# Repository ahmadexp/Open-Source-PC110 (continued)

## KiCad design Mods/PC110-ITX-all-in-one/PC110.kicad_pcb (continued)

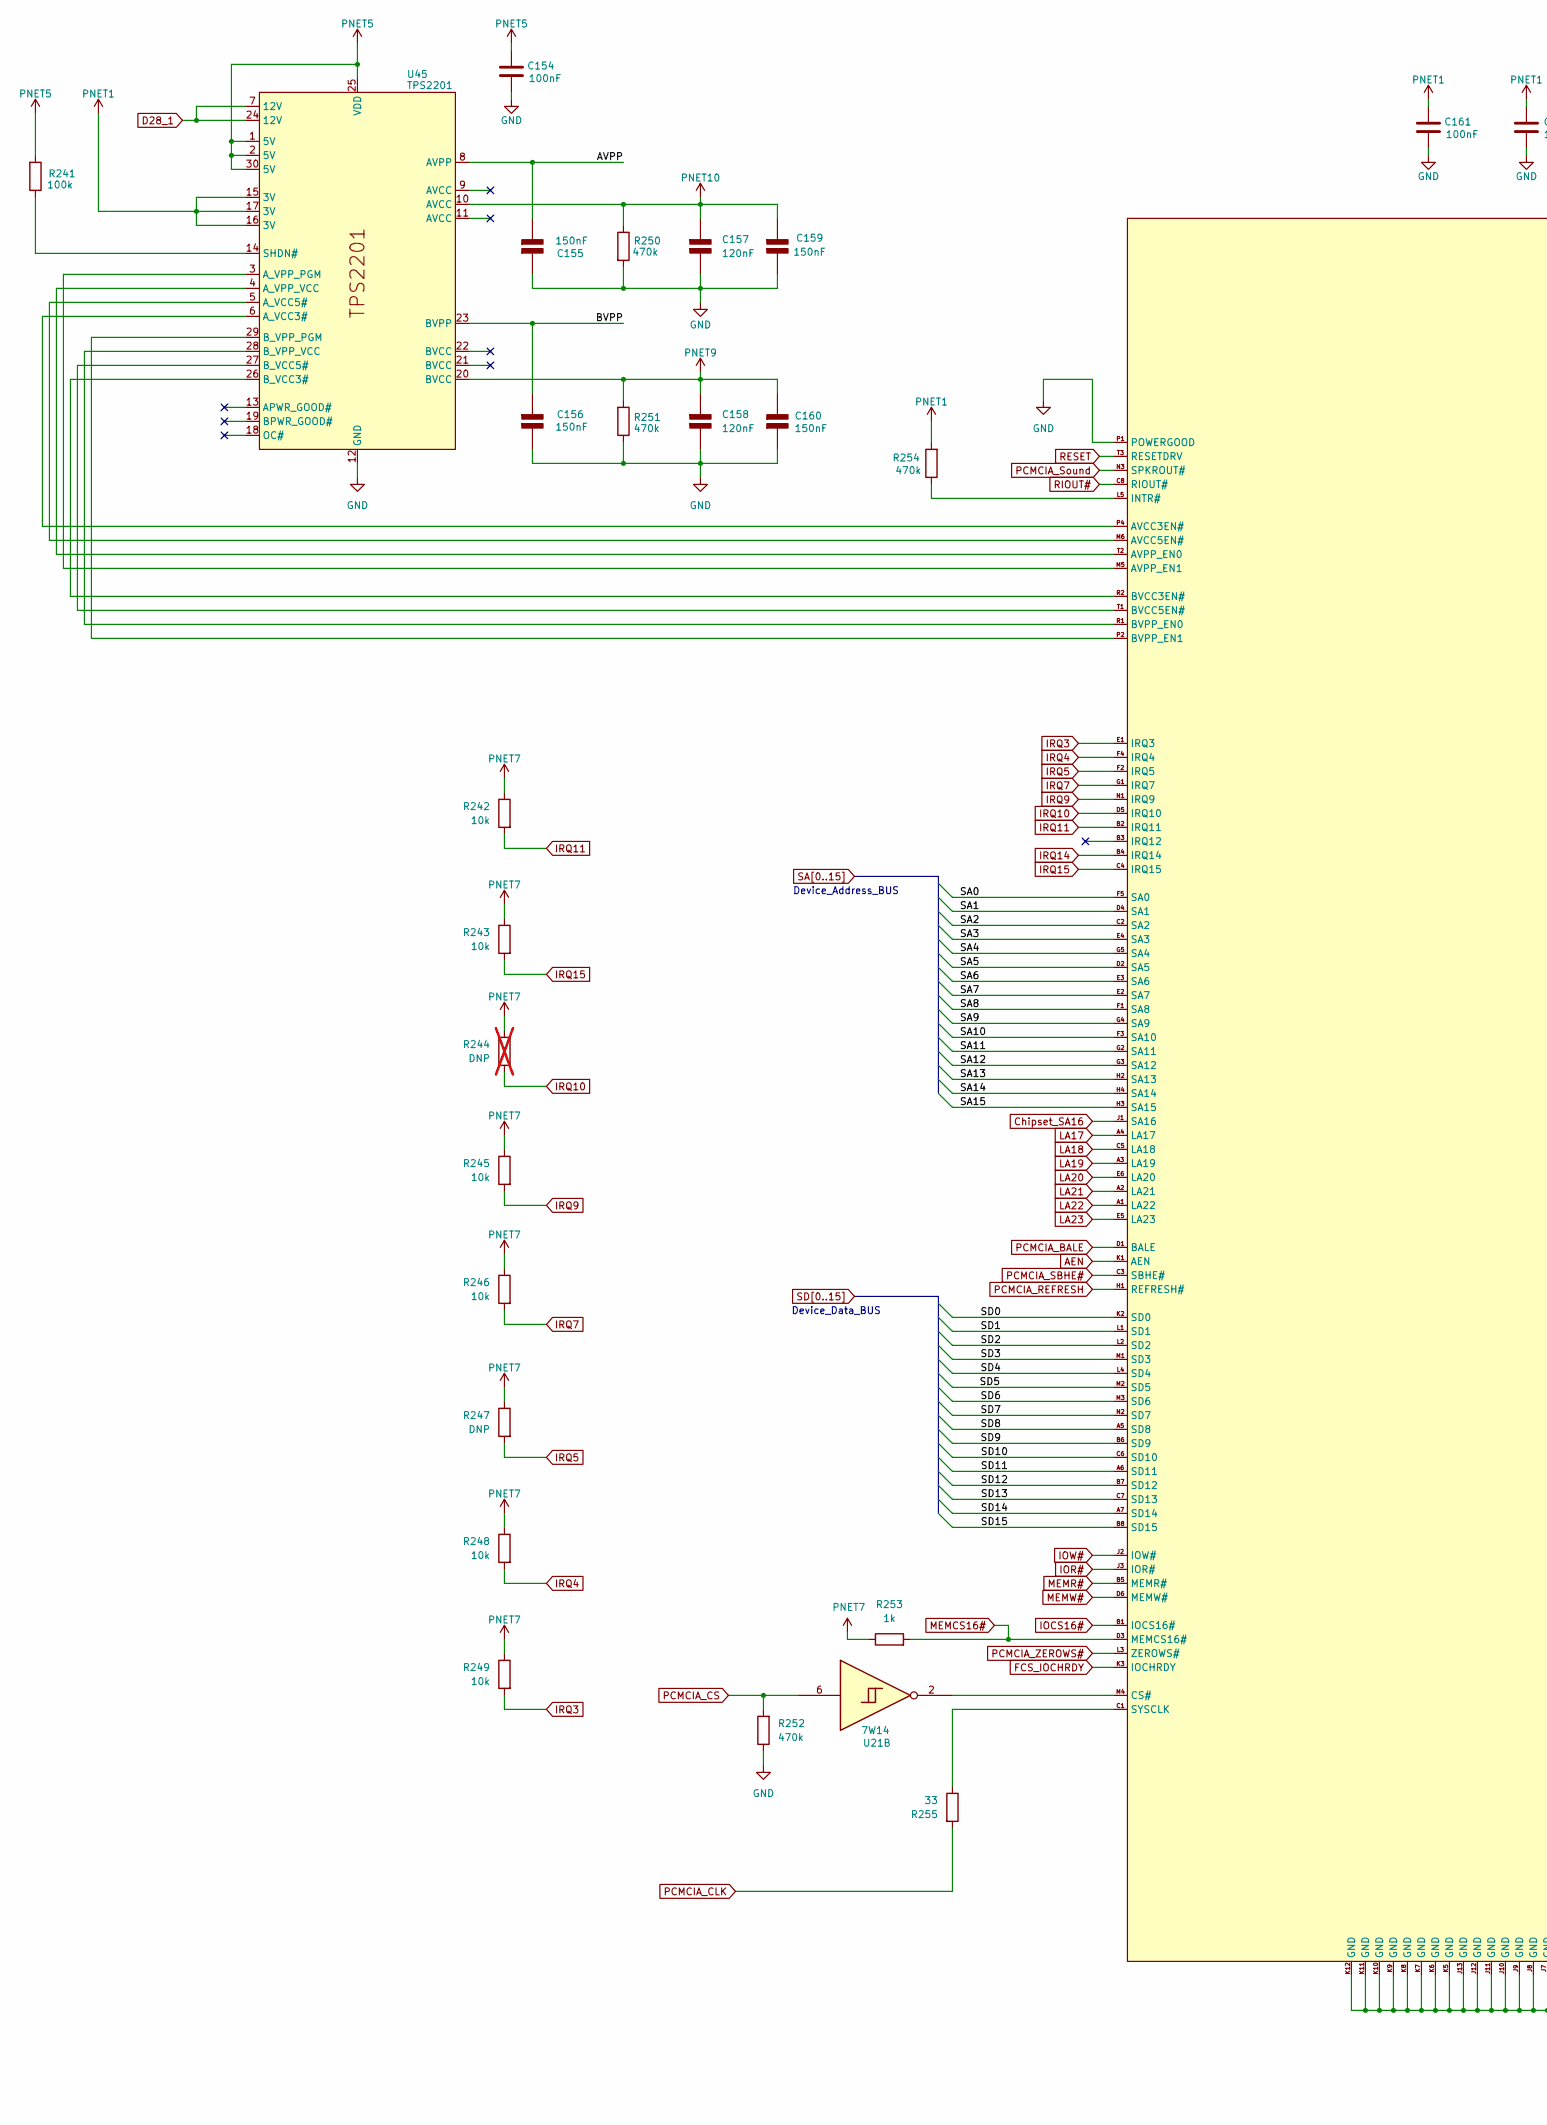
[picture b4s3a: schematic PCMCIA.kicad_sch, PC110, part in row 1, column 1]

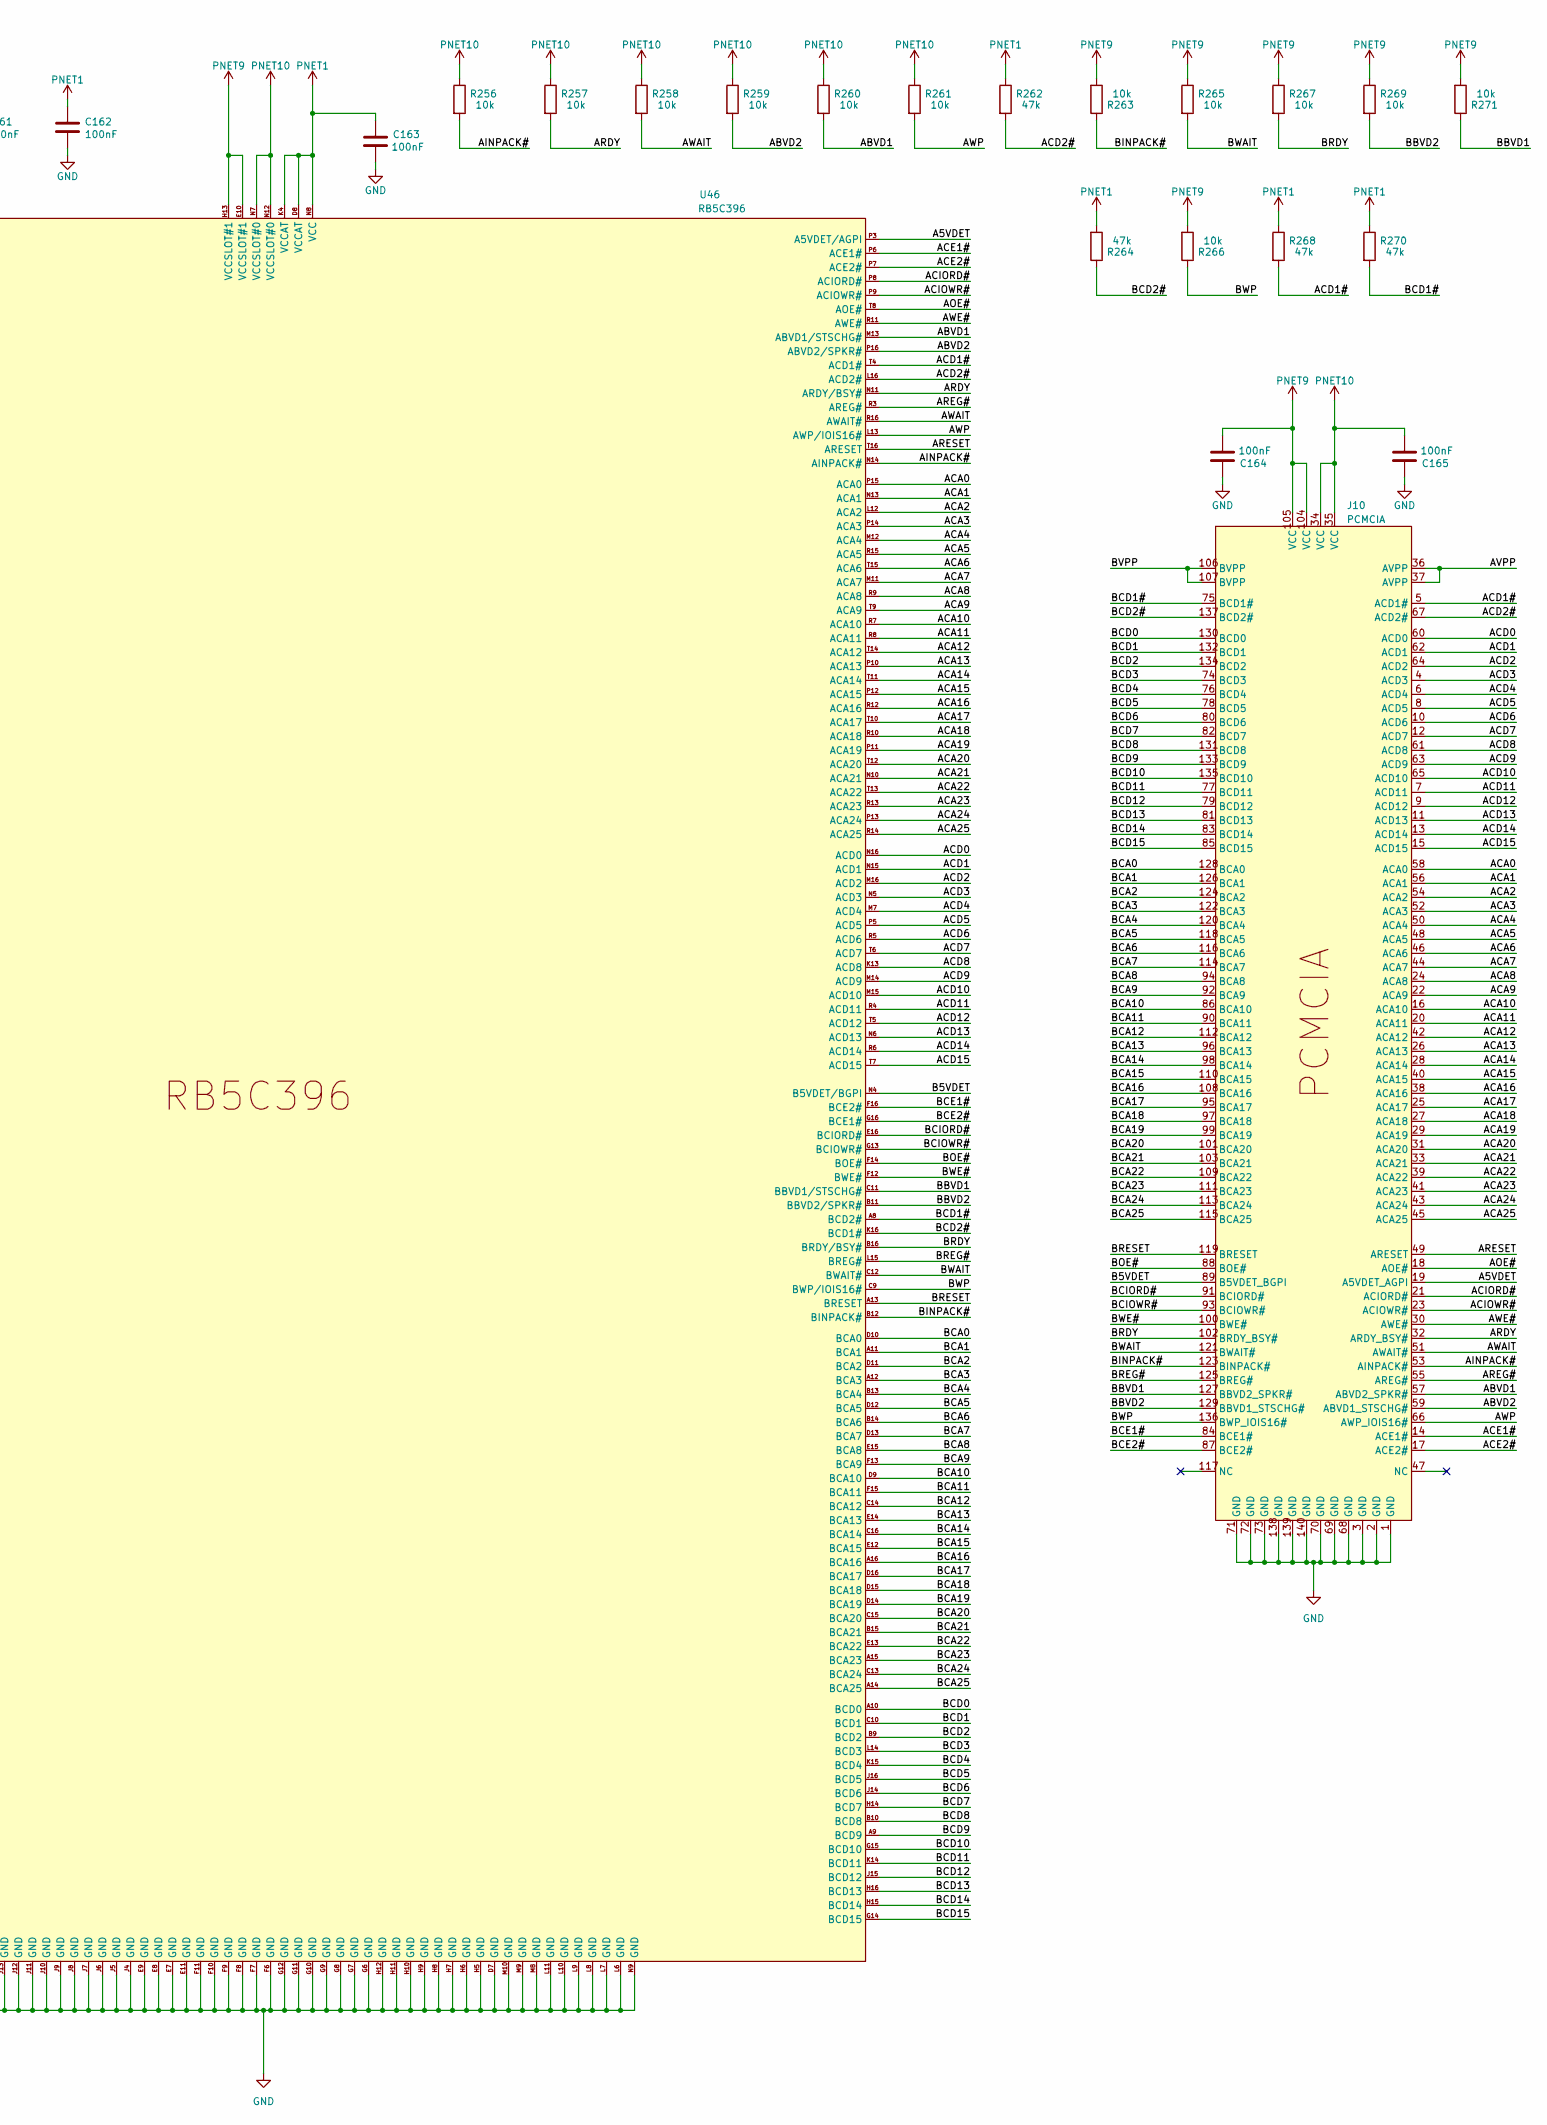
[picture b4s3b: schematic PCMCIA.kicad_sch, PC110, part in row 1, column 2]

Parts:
C154, C161, C162, C163, C164, C165: 100nF; C_0402_1005Metric
C155, C156: 150nF; C_0603_1608Metric
C157, C158: 120nF; C_0402_1005Metric
C159, C160: 150nF; C_0402_1005Metric
J10: PCMCIA
R241: 100k; R_0402_1005Metric
R242, R243, R245, R246, R248, R249, R256, R257, R258, R259, R260, R261, R263, R265, R266, R267, R269, R271: 10k; R_0402_1005Metric
R244: DNP; R_0402_1005Metric; not fitted
R247: DNP; R_0402_1005Metric
R250, R251, R252, R254: 470k; R_0402_1005Metric
R253: 1k; R_0402_1005Metric
R255: 33; R_0402_1005Metric
R262, R264, R268, R270: 47k; R_0402_1005Metric
U21: 7W14; sso-8
U45: TPS2201; TSSOP-30_6.1x9.7mm_P0.65mm
U46: RB5C396; BGA-256

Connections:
/PCMCIA/A5VDET: J10.19 (A5VDET_AGPI), U46.P3 (A5VDET/AGPI)
/PCMCIA/ABVD1: J10.57 (ABVD2_SPKR#), R260.2, U46.M13 (ABVD1/STSCHG#)
/PCMCIA/ABVD2: J10.59 (ABVD1_STSCHG#), R259.2, U46.P16 (ABVD2/SPKR#)
/PCMCIA/ACA0: J10.58 (ACA0), U46.P15 (ACA0)
/PCMCIA/ACA1: J10.56 (ACA1), U46.N13 (ACA1)
/PCMCIA/ACA2: J10.54 (ACA2), U46.L12 (ACA2)
/PCMCIA/ACA3: J10.52 (ACA3), U46.P14 (ACA3)
/PCMCIA/ACA4: J10.50 (ACA4), U46.M12 (ACA4)
/PCMCIA/ACA5: J10.48 (ACA5), U46.R15 (ACA5)
/PCMCIA/ACA6: J10.46 (ACA6), U46.T15 (ACA6)
/PCMCIA/ACA7: J10.44 (ACA7), U46.M11 (ACA7)
/PCMCIA/ACA8: J10.24 (ACA8), U46.R9 (ACA8)
/PCMCIA/ACA9: J10.22 (ACA9), U46.T9 (ACA9)
/PCMCIA/ACA10: J10.16 (ACA10), U46.R7 (ACA10)
/PCMCIA/ACA11: J10.20 (ACA11), U46.R8 (ACA11)
/PCMCIA/ACA12: J10.42 (ACA12), U46.T14 (ACA12)
/PCMCIA/ACA13: J10.26 (ACA13), U46.P10 (ACA13)
/PCMCIA/ACA14: J10.28 (ACA14), U46.T11 (ACA14)
/PCMCIA/ACA15: J10.40 (ACA15), U46.P12 (ACA15)
/PCMCIA/ACA16: J10.38 (ACA16), U46.R12 (ACA16)
/PCMCIA/ACA17: J10.25 (ACA17), U46.T10 (ACA17)
/PCMCIA/ACA18: J10.27 (ACA18), U46.R10 (ACA18)
/PCMCIA/ACA19: J10.29 (ACA19), U46.P11 (ACA19)
/PCMCIA/ACA20: J10.31 (ACA20), U46.T12 (ACA20)
/PCMCIA/ACA21: J10.33 (ACA21), U46.N10 (ACA21)
/PCMCIA/ACA22: J10.39 (ACA22), U46.T13 (ACA22)
/PCMCIA/ACA23: J10.41 (ACA23), U46.R13 (ACA23)
/PCMCIA/ACA24: J10.43 (ACA24), U46.P13 (ACA24)
/PCMCIA/ACA25: J10.45 (ACA25), U46.R14 (ACA25)
/PCMCIA/ACD0: J10.60 (ACD0), U46.N16 (ACD0)
/PCMCIA/ACD1: J10.62 (ACD1), U46.N15 (ACD1)
/PCMCIA/ACD1#: J10.5 (ACD1#), R268.2, U46.T4 (ACD1#)
/PCMCIA/ACD2: J10.64 (ACD2), U46.M16 (ACD2)
/PCMCIA/ACD2#: J10.67 (ACD2#), R262.2, U46.L16 (ACD2#)
/PCMCIA/ACD3: J10.4 (ACD3), U46.N5 (ACD3)
/PCMCIA/ACD4: J10.6 (ACD4), U46.M7 (ACD4)
/PCMCIA/ACD5: J10.8 (ACD5), U46.P5 (ACD5)
/PCMCIA/ACD6: J10.10 (ACD6), U46.R5 (ACD6)
/PCMCIA/ACD7: J10.12 (ACD7), U46.T6 (ACD7)
/PCMCIA/ACD8: J10.61 (ACD8), U46.K13 (ACD8)
/PCMCIA/ACD9: J10.63 (ACD9), U46.M14 (ACD9)
/PCMCIA/ACD10: J10.65 (ACD10), U46.M15 (ACD10)
/PCMCIA/ACD11: J10.7 (ACD11), U46.R4 (ACD11)
/PCMCIA/ACD12: J10.9 (ACD12), U46.T5 (ACD12)
/PCMCIA/ACD13: J10.11 (ACD13), U46.N6 (ACD13)
/PCMCIA/ACD14: J10.13 (ACD14), U46.R6 (ACD14)
/PCMCIA/ACD15: J10.15 (ACD15), U46.T7 (ACD15)
/PCMCIA/ACE1#: J10.14 (ACE1#), U46.P6 (ACE1#)
/PCMCIA/ACE2#: J10.17 (ACE2#), U46.P7 (ACE2#)
/PCMCIA/ACIORD#: J10.21 (ACIORD#), U46.P8 (ACIORD#)
/PCMCIA/ACIOWR#: J10.23 (ACIOWR#), U46.P9 (ACIOWR#)
/PCMCIA/AINPACK#: J10.53 (AINPACK#), R256.2, U46.N14 (AINPACK#)
/PCMCIA/AOE#: J10.18 (AOE#), U46.T8 (AOE#)
/PCMCIA/ARDY: J10.32 (ARDY_BSY#), R257.2, U46.N11 (ARDY/BSY#)
/PCMCIA/AREG#: J10.55 (AREG#), U46.R3 (AREG#)
/PCMCIA/ARESET: J10.49 (ARESET), U46.T16 (ARESET)
/PCMCIA/AVPP: C155.2 (-), J10.36 (AVPP), J10.37 (AVPP), U45.8 (AVPP)
/PCMCIA/AWAIT: J10.51 (AWAIT#), R258.2, U46.R16 (AWAIT#)
/PCMCIA/AWE#: J10.30 (AWE#), U46.R11 (AWE#)
/PCMCIA/AWP: J10.66 (AWP_IOIS16#), R261.2, U46.L13 (AWP/IOIS16#)
/PCMCIA/B5VDET: J10.89 (B5VDET_BGPI), U46.N4 (B5VDET/BGPI)
/PCMCIA/BBVD1: J10.127 (BBVD2_SPKR#), R271.1, U46.C11 (BBVD1/STSCHG#)
/PCMCIA/BBVD2: J10.129 (BBVD1_STSCHG#), R269.2, U46.B11 (BBVD2/SPKR#)
/PCMCIA/BCA0: J10.128 (BCA0), U46.D10 (BCA0)
/PCMCIA/BCA1: J10.126 (BCA1), U46.A11 (BCA1)
/PCMCIA/BCA2: J10.124 (BCA2), U46.D11 (BCA2)
/PCMCIA/BCA3: J10.122 (BCA3), U46.A12 (BCA3)
/PCMCIA/BCA4: J10.120 (BCA4), U46.B13 (BCA4)
/PCMCIA/BCA5: J10.118 (BCA5), U46.D12 (BCA5)
/PCMCIA/BCA6: J10.116 (BCA6), U46.B14 (BCA6)
/PCMCIA/BCA7: J10.114 (BCA7), U46.D13 (BCA7)
/PCMCIA/BCA8: J10.94 (BCA8), U46.E15 (BCA8)
/PCMCIA/BCA9: J10.92 (BCA9), U46.F13 (BCA9)
/PCMCIA/BCA10: J10.86 (BCA10), U46.D9 (BCA10)
/PCMCIA/BCA11: J10.90 (BCA11), U46.F15 (BCA11)
/PCMCIA/BCA12: J10.112 (BCA12), U46.C14 (BCA12)
/PCMCIA/BCA13: J10.96 (BCA13), U46.E14 (BCA13)
/PCMCIA/BCA14: J10.98 (BCA14), U46.C16 (BCA14)
/PCMCIA/BCA15: J10.110 (BCA15), U46.E12 (BCA15)
/PCMCIA/BCA16: J10.108 (BCA16), U46.A16 (BCA16)
/PCMCIA/BCA17: J10.95 (BCA17), U46.D16 (BCA17)
/PCMCIA/BCA18: J10.97 (BCA18), U46.D15 (BCA18)
/PCMCIA/BCA19: J10.99 (BCA19), U46.D14 (BCA19)
/PCMCIA/BCA20: J10.101 (BCA20), U46.C15 (BCA20)
/PCMCIA/BCA21: J10.103 (BCA21), U46.B15 (BCA21)
/PCMCIA/BCA22: J10.109 (BCA22), U46.E13 (BCA22)
/PCMCIA/BCA23: J10.111 (BCA23), U46.A15 (BCA23)
/PCMCIA/BCA24: J10.113 (BCA24), U46.C13 (BCA24)
/PCMCIA/BCA25: J10.115 (BCA25), U46.A14 (BCA25)
/PCMCIA/BCD0: J10.130 (BCD0), U46.A10 (BCD0)
/PCMCIA/BCD1: J10.132 (BCD1), U46.C10 (BCD1)
/PCMCIA/BCD1#: J10.75 (BCD1#), R270.2, U46.A8 (BCD2#)
/PCMCIA/BCD2: J10.134 (BCD2), U46.B9 (BCD2)
/PCMCIA/BCD2#: J10.137 (BCD2#), R264.1, U46.K16 (BCD1#)
/PCMCIA/BCD3: J10.74 (BCD3), U46.L14 (BCD3)
/PCMCIA/BCD4: J10.76 (BCD4), U46.K15 (BCD4)
/PCMCIA/BCD5: J10.78 (BCD5), U46.J16 (BCD5)
/PCMCIA/BCD6: J10.80 (BCD6), U46.J14 (BCD6)
/PCMCIA/BCD7: J10.82 (BCD7), U46.H14 (BCD7)
/PCMCIA/BCD8: J10.131 (BCD8), U46.B10 (BCD8)
/PCMCIA/BCD9: J10.133 (BCD9), U46.A9 (BCD9)
/PCMCIA/BCD10: J10.135 (BCD10), U46.G15 (BCD10)
/PCMCIA/BCD11: J10.77 (BCD11), U46.K14 (BCD11)
/PCMCIA/BCD12: J10.79 (BCD12), U46.J15 (BCD12)
/PCMCIA/BCD13: J10.81 (BCD13), U46.H16 (BCD13)
/PCMCIA/BCD14: J10.83 (BCD14), U46.H15 (BCD14)
/PCMCIA/BCD15: J10.85 (BCD15), U46.G14 (BCD15)
/PCMCIA/BCE1#: J10.84 (BCE1#), U46.F16 (BCE2#)
/PCMCIA/BCE2#: J10.87 (BCE2#), U46.G16 (BCE1#)
/PCMCIA/BCIORD#: J10.91 (BCIORD#), U46.E16 (BCIORD#)
/PCMCIA/BCIOWR#: J10.93 (BCIOWR#), U46.G13 (BCIOWR#)
/PCMCIA/BINPACK#: J10.123 (BINPACK#), R263.1, U46.B12 (BINPACK#)
/PCMCIA/BOE#: J10.88 (BOE#), U46.F14 (BOE#)
/PCMCIA/BRDY: J10.102 (BRDY_BSY#), R267.2, U46.B16 (BRDY/BSY#)
/PCMCIA/BREG#: J10.125 (BREG#), U46.L15 (BREG#)
/PCMCIA/BRESET: J10.119 (BRESET), U46.A13 (BRESET)
/PCMCIA/BVPP: C156.1 (+), J10.106 (BVPP), J10.107 (BVPP), U45.23 (BVPP)
/PCMCIA/BWAIT: J10.121 (BWAIT#), R265.2, U46.C12 (BWAIT#)
/PCMCIA/BWE#: J10.100 (BWE#), U46.F12 (BWE#)
/PCMCIA/BWP: J10.136 (BWP_IOIS16#), R266.1, U46.C9 (BWP/IOIS16#)
AEN: U46.K1 (AEN); also elsewhere on the board
Chipset_SA16: U46.J1 (SA16); also elsewhere on the board
D28_1: U45.7 (12V), U45.24 (12V); also elsewhere on the board
FCS_IOCHRDY: U46.K3 (IOCHRDY); also elsewhere on the board
GND: C154.2, C155.1 (+), C156.2 (-), C157.2 (-), C158.2 (-), C159.2 (-), C160.1 (+), C161.2, C162.2, C163.1, C164.2, C165.2, J10.1 (GND), J10.2 (GND), J10.3 (GND), J10.68 (GND), J10.69 (GND), J10.70 (GND), J10.71 (GND), J10.72 (GND), J10.73 (GND), J10.138 (GND), J10.139 (GND), J10.140 (GND), R250.2, R251.1, R252.1, U45.12 (GND), U46.D7 (GND), U46.E7 (GND), U46.E8 (GND), U46.E9 (GND), U46.E11 (GND), U46.F6 (GND), U46.F7 (GND), U46.F8 (GND), U46.F9 (GND), U46.F10 (GND), U46.F11 (GND), U46.G6 (GND), U46.G7 (GND), U46.G8 (GND), U46.G9 (GND), U46.G10 (GND), U46.G11 (GND), U46.G12 (GND), U46.H5 (GND), U46.H6 (GND), U46.H7 (GND), U46.H8 (GND), U46.H9 (GND), U46.H10 (GND), U46.H11 (GND), U46.H12 (GND), U46.J4 (GND), U46.J5 (GND), U46.J6 (GND), U46.J7 (GND), U46.J8 (GND), U46.J9 (GND), U46.J10 (GND), U46.J11 (GND), U46.J12 (GND), U46.J13 (GND), U46.K5 (GND), U46.K6 (GND), U46.K7 (GND), U46.K8 (GND), U46.K9 (GND), U46.K10 (GND), U46.K11 (GND), U46.K12 (GND), U46.L6 (GND), U46.L7 (GND), U46.L8 (GND), U46.L9 (GND), U46.L10 (GND), U46.L11 (GND), U46.M8 (GND), U46.M9 (GND), U46.M10 (GND), U46.N9 (GND), U46.P1 (POWERGOOD); also elsewhere on the board
IOCS16#: U46.B1 (IOCS16#); also elsewhere on the board
IOR#: U46.J3 (IOR#); also elsewhere on the board
IOW#: U46.J2 (IOW#); also elsewhere on the board
IRQ3: R249.2, U46.E1 (IRQ3); also elsewhere on the board
IRQ4: R248.2, U46.F4 (IRQ4); also elsewhere on the board
IRQ5: R247.2, U46.F2 (IRQ5); also elsewhere on the board
IRQ7: R246.2, U46.G1 (IRQ7); also elsewhere on the board
IRQ9: R245.2, U46.N1 (IRQ9); also elsewhere on the board
IRQ10: R244.2, U46.D5 (IRQ10); also elsewhere on the board
IRQ11: R242.2, U46.B2 (IRQ11); also elsewhere on the board
IRQ14: U46.B4 (IRQ14); also elsewhere on the board
IRQ15: R243.2, U46.C4 (IRQ15); also elsewhere on the board
LA17: U46.A4 (LA17); also elsewhere on the board
LA18: U46.C5 (LA18); also elsewhere on the board
LA19: U46.A3 (LA19); also elsewhere on the board
LA20: U46.E6 (LA20); also elsewhere on the board
LA21: U46.A2 (LA21); also elsewhere on the board
LA22: U46.A1 (LA22); also elsewhere on the board
LA23: U46.E5 (LA23); also elsewhere on the board
MEMCS16#: R253.2, U46.D3 (MEMCS16#); also elsewhere on the board
MEMR#: U46.B5 (MEMR#); also elsewhere on the board
MEMW#: U46.D6 (MEMW#); also elsewhere on the board
unnamed: U45.6 (A_VCC3#), U46.P4 (AVCC3EN#)
unnamed: U45.5 (A_VCC5#), U46.M6 (AVCC5EN#)
unnamed: U45.3 (A_VPP_PGM), U46.M5 (AVPP_EN1)
unnamed: U45.4 (A_VPP_VCC), U46.T2 (AVPP_EN0)
unnamed: U45.26 (B_VCC3#), U46.R2 (BVCC3EN#)
unnamed: U45.27 (B_VCC5#), U46.T1 (BVCC5EN#)
unnamed: U45.29 (B_VPP_PGM), U46.P2 (BVPP_EN1)
unnamed: U45.28 (B_VPP_VCC), U46.R1 (BVPP_EN0)
unnamed: R241.1, U45.14 (SHDN#)
unnamed: U21.2, U46.M4 (CS#)
unnamed: R254.1, U46.L5 (INTR#)
unnamed: R255.1, U46.C1 (SYSCLK)
PCMCIA_BALE: U46.D1 (BALE); also elsewhere on the board
PCMCIA_CLK: R255.2; also elsewhere on the board
PCMCIA_CS: R252.2, U21.6; also elsewhere on the board
PCMCIA_REFRESH: U46.H1 (REFRESH#); also elsewhere on the board
PCMCIA_SBHE#: U46.C3 (SBHE#); also elsewhere on the board
PCMCIA_Sound: U46.N3 (SPKROUT#); also elsewhere on the board
PCMCIA_ZEROWS#: U46.L3 (ZEROWS#); also elsewhere on the board
PNET1: C161.1, C162.1, C163.2, R254.2, R262.1, R264.2, R268.1, R270.1, U45.15 (3V), U45.16 (3V), U45.17 (3V), U46.D8 (VCCAT), U46.K4 (VCCAT), U46.N8 (VCC); also elsewhere on the board
PNET5: C154.1, R241.2, U45.1 (5V), U45.2 (5V), U45.25 (VDD), U45.30 (5V); also elsewhere on the board
PNET7: R242.1, R243.1, R244.1, R245.1, R246.1, R247.1, R248.1, R249.1, R253.1; also elsewhere on the board
PNET9: C158.1 (+), C160.2 (-), C164.1, J10.104 (VCC), J10.105 (VCC), R251.2, R263.2, R265.1, R266.2, R267.1, R269.1, R271.2, U45.20 (BVCC), U46.E10 (VCCSLOT#1), U46.H13 (VCCSLOT#1)
PNET10: C157.1 (+), C159.1 (+), C165.1, J10.34 (VCC), J10.35 (VCC), R250.1, R256.1, R257.1, R258.1, R259.1, R260.1, R261.1, U45.10 (AVCC), U46.N7 (VCCSLOT#0), U46.N12 (VCCSLOT#0)
RESET: U46.T3 (RESETDRV); also elsewhere on the board
RIOUT#: U46.C8 (RIOUT#); also elsewhere on the board
SA0: U46.F5 (SA0); also elsewhere on the board
SA1: U46.D4 (SA1); also elsewhere on the board
SA2: U46.C2 (SA2); also elsewhere on the board
SA3: U46.E4 (SA3); also elsewhere on the board
SA4: U46.G5 (SA4); also elsewhere on the board
SA5: U46.D2 (SA5); also elsewhere on the board
SA6: U46.E3 (SA6); also elsewhere on the board
SA7: U46.E2 (SA7); also elsewhere on the board
SA8: U46.F1 (SA8); also elsewhere on the board
SA9: U46.G4 (SA9); also elsewhere on the board
SA10: U46.F3 (SA10); also elsewhere on the board
SA11: U46.G2 (SA11); also elsewhere on the board
SA12: U46.G3 (SA12); also elsewhere on the board
SA13: U46.H2 (SA13); also elsewhere on the board
SA14: U46.H4 (SA14); also elsewhere on the board
SA15: U46.H3 (SA15); also elsewhere on the board
SD0: U46.K2 (SD0); also elsewhere on the board
SD1: U46.L1 (SD1); also elsewhere on the board
SD2: U46.L2 (SD2); also elsewhere on the board
SD3: U46.M1 (SD3); also elsewhere on the board
SD4: U46.L4 (SD4); also elsewhere on the board
SD5: U46.M2 (SD5); also elsewhere on the board
SD6: U46.M3 (SD6); also elsewhere on the board
SD7: U46.N2 (SD7); also elsewhere on the board
SD8: U46.A5 (SD8); also elsewhere on the board
SD9: U46.B6 (SD9); also elsewhere on the board
SD10: U46.C6 (SD10); also elsewhere on the board
SD11: U46.A6 (SD11); also elsewhere on the board
SD12: U46.B7 (SD12); also elsewhere on the board
SD13: U46.C7 (SD13); also elsewhere on the board
SD14: U46.A7 (SD14); also elsewhere on the board
SD15: U46.B8 (SD15); also elsewhere on the board

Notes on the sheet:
Device_Data_BUS
Device_Address_BUS

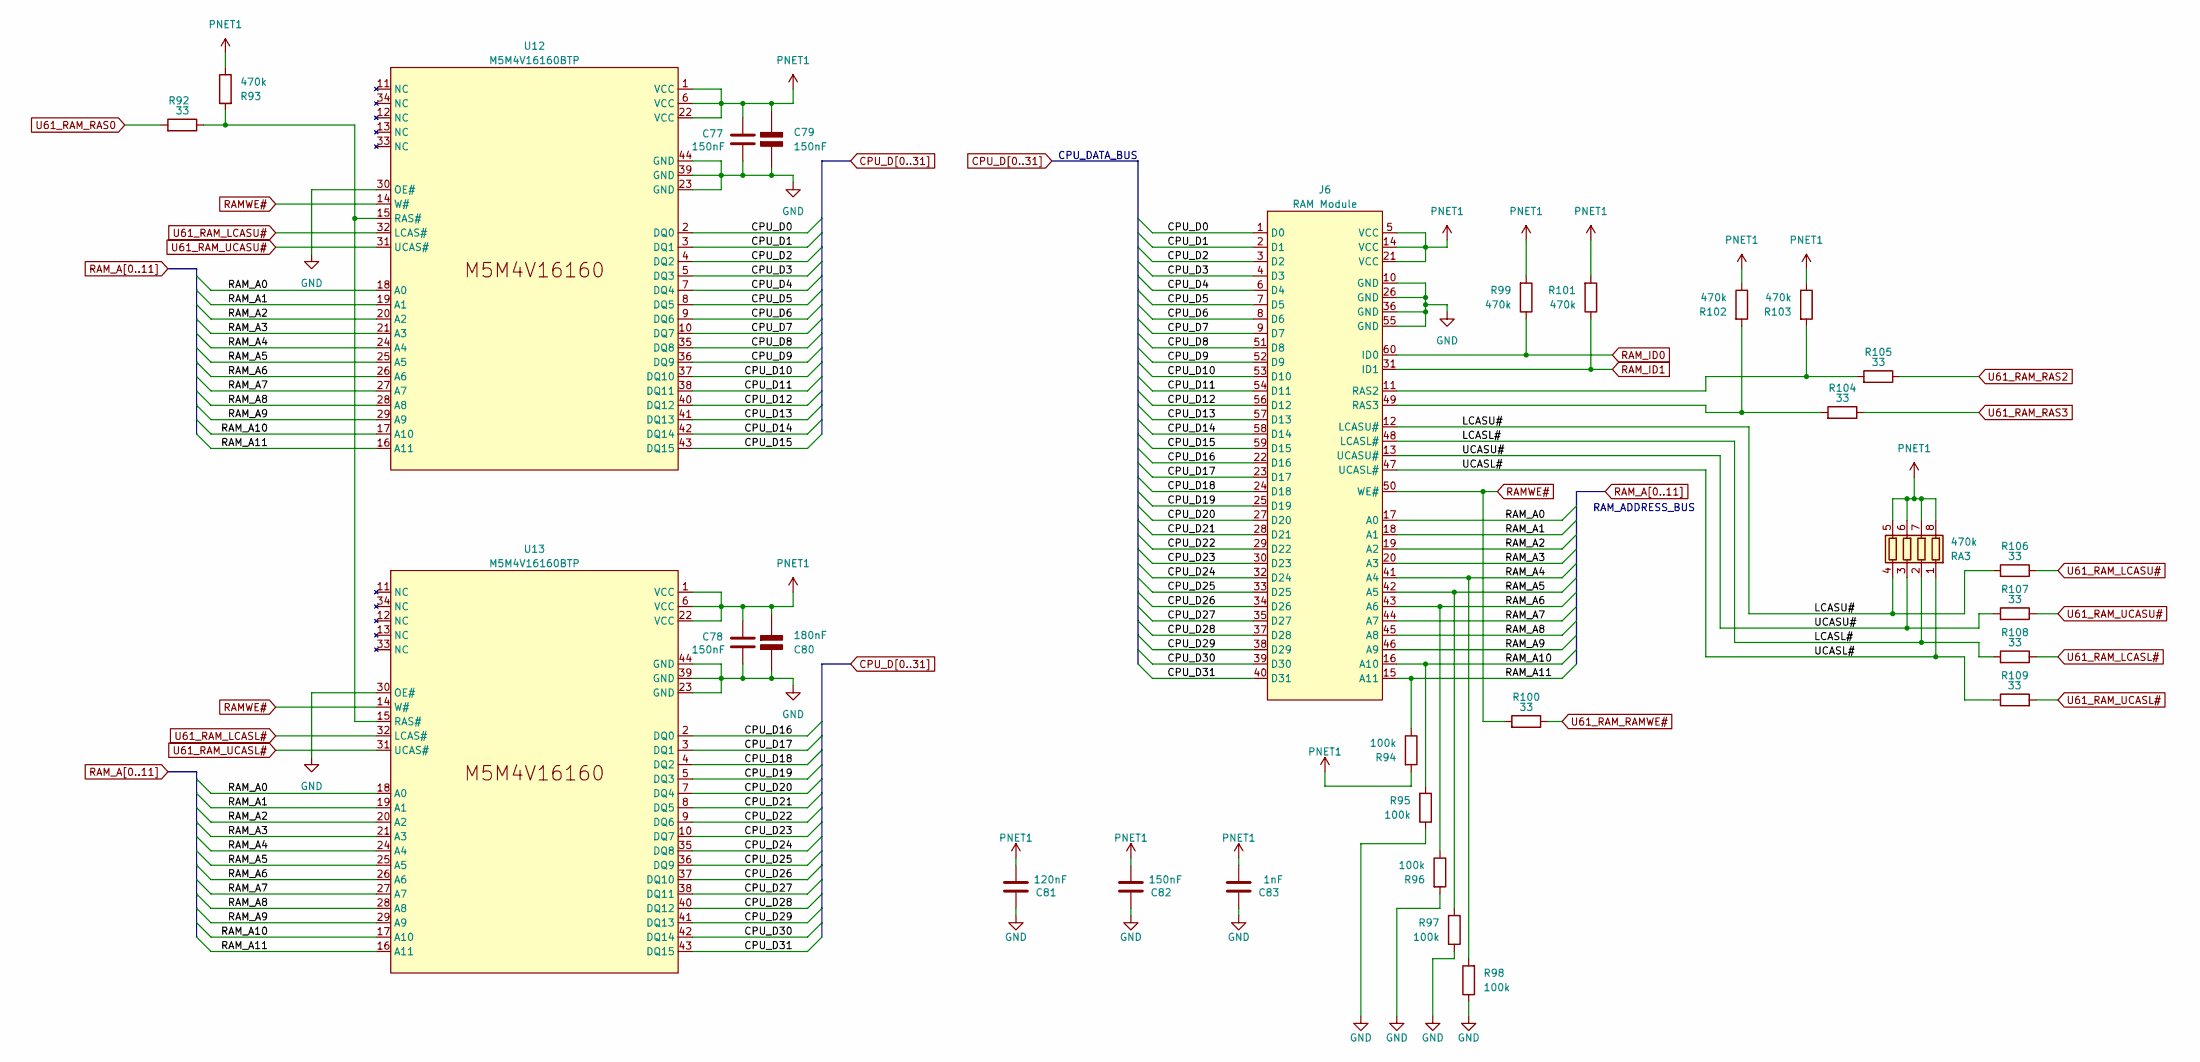
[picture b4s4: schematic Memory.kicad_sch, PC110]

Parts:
C77, C78, C79, C82: 150nF; C_0402_1005Metric
C80: 180nF; C_0402_1005Metric
C81: 120nF; C_0402_1005Metric
C83: 1nF; C_0402_1005Metric
J6: RAM Module
R92, R100, R104, R105, R106, R107, R108, R109: 33; R_0402_1005Metric
R93, R99, R101, R102, R103: 470k; R_0402_1005Metric
R94, R95, R96, R97, R98: 100k; R_0402_1005Metric
RA3: 470k; R-array
U12, U13: M5M4V16160BTP; RAMchip

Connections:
/Memory/LCASL#: J6.48 (LCASL#), R108.2, RA3.2 (R2.1)
/Memory/LCASU#: J6.12 (LCASU#), R106.2, RA3.4 (R4.1)
/Memory/UCASL#: J6.47 (UCASL#), R109.1, RA3.1 (R1.1)
/Memory/UCASU#: J6.13 (UCASU#), R107.2, RA3.3 (R3.1)
CPU_D0: J6.1 (D0), U12.2 (DQ0); also elsewhere on the board
CPU_D1: J6.2 (D1), U12.3 (DQ1); also elsewhere on the board
CPU_D2: J6.3 (D2), U12.4 (DQ2); also elsewhere on the board
CPU_D3: J6.4 (D3), U12.5 (DQ3); also elsewhere on the board
CPU_D4: J6.6 (D4), U12.7 (DQ4); also elsewhere on the board
CPU_D5: J6.7 (D5), U12.8 (DQ5); also elsewhere on the board
CPU_D6: J6.8 (D6), U12.9 (DQ6); also elsewhere on the board
CPU_D7: J6.9 (D7), U12.10 (DQ7); also elsewhere on the board
CPU_D8: J6.51 (D8), U12.35 (DQ8); also elsewhere on the board
CPU_D9: J6.52 (D9), U12.36 (DQ9); also elsewhere on the board
CPU_D10: J6.53 (D10), U12.37 (DQ10); also elsewhere on the board
CPU_D11: J6.54 (D11), U12.38 (DQ11); also elsewhere on the board
CPU_D12: J6.56 (D12), U12.40 (DQ12); also elsewhere on the board
CPU_D13: J6.57 (D13), U12.41 (DQ13); also elsewhere on the board
CPU_D14: J6.58 (D14), U12.42 (DQ14); also elsewhere on the board
CPU_D15: J6.59 (D15), U12.43 (DQ15); also elsewhere on the board
CPU_D16: J6.22 (D16), U13.2 (DQ0); also elsewhere on the board
CPU_D17: J6.23 (D17), U13.3 (DQ1); also elsewhere on the board
CPU_D18: J6.24 (D18), U13.4 (DQ2); also elsewhere on the board
CPU_D19: J6.25 (D19), U13.5 (DQ3); also elsewhere on the board
CPU_D20: J6.27 (D20), U13.7 (DQ4); also elsewhere on the board
CPU_D21: J6.28 (D21), U13.8 (DQ5); also elsewhere on the board
CPU_D22: J6.29 (D22), U13.9 (DQ6); also elsewhere on the board
CPU_D23: J6.30 (D23), U13.10 (DQ7); also elsewhere on the board
CPU_D24: J6.32 (D24), U13.35 (DQ8); also elsewhere on the board
CPU_D25: J6.33 (D25), U13.36 (DQ9); also elsewhere on the board
CPU_D26: J6.34 (D26), U13.37 (DQ10); also elsewhere on the board
CPU_D27: J6.35 (D27), U13.38 (DQ11); also elsewhere on the board
CPU_D28: J6.37 (D28), U13.40 (DQ12); also elsewhere on the board
CPU_D29: J6.38 (D29), U13.41 (DQ13); also elsewhere on the board
CPU_D30: J6.39 (D30), U13.42 (DQ14); also elsewhere on the board
CPU_D31: J6.40 (D31), U13.43 (DQ15); also elsewhere on the board
GND: C77.2, C78.2, C79.2 (-), C80.1 (+), C81.1, C82.1, C83.1, J6.10 (GND), J6.26 (GND), J6.36 (GND), J6.55 (GND), R95.1, R96.2, R97.1, R98.1, U12.23 (GND), U12.30 (OE#), U12.39 (GND), U12.44 (GND), U13.23 (GND), U13.30 (OE#), U13.39 (GND), U13.44 (GND); also elsewhere on the board
unnamed: J6.11 (RAS2), R103.2, R105.2
unnamed: J6.49 (RAS3), R102.2, R104.2
unnamed: R92.1, R93.2, U12.15 (RAS#), U13.15 (RAS#)
PNET1: C77.1, C78.1, C79.1 (+), C80.2 (-), C81.2, C82.2, C83.2, J6.5 (VCC), J6.14 (VCC), J6.21 (VCC), R93.1, R94.2, R99.2, R101.2, R102.1, R103.1, RA3.5 (R4.2), RA3.6 (R3.2), RA3.7 (R2.2), RA3.8 (R1.2), U12.1 (VCC), U12.6 (VCC), U12.22 (VCC), U13.1 (VCC), U13.6 (VCC), U13.22 (VCC); also elsewhere on the board
RAMWE#: J6.50 (WE#), R100.2, U12.14 (W#), U13.14 (W#)
RAM_A0: J6.17 (A0), U12.18 (A0), U13.18 (A0); also elsewhere on the board
RAM_A1: J6.18 (A1), U12.19 (A1), U13.19 (A1); also elsewhere on the board
RAM_A2: J6.19 (A2), U12.20 (A2), U13.20 (A2); also elsewhere on the board
RAM_A3: J6.20 (A3), U12.21 (A3), U13.21 (A3); also elsewhere on the board
RAM_A4: J6.41 (A4), R98.2, U12.24 (A4), U13.24 (A4); also elsewhere on the board
RAM_A5: J6.42 (A5), R97.2, U12.25 (A5), U13.25 (A5); also elsewhere on the board
RAM_A6: J6.43 (A6), R96.1, U12.26 (A6), U13.26 (A6); also elsewhere on the board
RAM_A7: J6.44 (A7), U12.27 (A7), U13.27 (A7); also elsewhere on the board
RAM_A8: J6.45 (A8), U12.28 (A8), U13.28 (A8); also elsewhere on the board
RAM_A9: J6.46 (A9), U12.29 (A9), U13.29 (A9); also elsewhere on the board
RAM_A10: J6.16 (A10), R95.2, U12.17 (A10), U13.17 (A10); also elsewhere on the board
RAM_A11: J6.15 (A11), R94.1, U12.16 (A11), U13.16 (A11); also elsewhere on the board
RAM_ID0: J6.60 (ID0), R99.1; also elsewhere on the board
RAM_ID1: J6.31 (ID1), R101.1; also elsewhere on the board
U61_RAM_LCASL#: R108.1, U13.32 (LCAS#); also elsewhere on the board
U61_RAM_LCASU#: R106.1, U12.32 (LCAS#); also elsewhere on the board
U61_RAM_RAMWE#: R100.1; also elsewhere on the board
U61_RAM_RAS0: R92.2; also elsewhere on the board
U61_RAM_RAS2: R105.1; also elsewhere on the board
U61_RAM_RAS3: R104.1; also elsewhere on the board
U61_RAM_UCASL#: R109.2, U13.31 (UCAS#); also elsewhere on the board
U61_RAM_UCASU#: R107.1, U12.31 (UCAS#); also elsewhere on the board

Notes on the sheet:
RAM_ADDRESS_BUS
CPU_DATA_BUS
